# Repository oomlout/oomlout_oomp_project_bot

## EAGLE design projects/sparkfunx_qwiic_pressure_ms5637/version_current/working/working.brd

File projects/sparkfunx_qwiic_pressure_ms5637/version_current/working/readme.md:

# OOMP Project  
## Qwiic_Pressure-MS5637  by sparkfunX  
  
oomp key: oomp_projects_flat_sparkfunx_qwiic_pressure_ms5637  
(snippet of original readme)  
  
SparkFun Qwiic Pressure with MS5637  
========================================  

[*SparkX Pressure Sensor (Qwiic) - MS5637 (SPX-14688)*](https://www.sparkfun.com/products/14688)  
  
MEMs based barometric pressure sensors are quite common these days. The Qwiic Pressure Sensor with the MS5637 shines by being the most sensitive barometric pressure sensor we have come across. It is capable of detecting the difference in 13cm of air! And the MS5637 is low cost and easy to use.  
  
The Qwiic Pressure Sensor for the MS5637 is a very sensitive, fully calibrated, low power, easy to use barometric pressure sensor capable of detecting a change of as little as 13cm of air! The Qwiic Pressure Sensor is perfect for home weather stations, detecting changes in altitude, and pneumatic based switches or actuators.  
  
The original manufacturer TE has written a great Arduino library for the device. We've added a heap of examples and new functions to make the sensor even easier to use. Search the Arduino Library manager for 'SparkFun MS5637' to get the latest library features.  
  
This board is one of our many [Qwiic](https://www.sparkfun.com/qwiic) compatible boards! Simply plug and go. No soldering, no figuring out which is SDA or SCL, and no voltage regulation or translation required!  
  
SparkFun labored with love to create this code. Feel like supporting open source ha  
  full source readme at [readme_src.md](readme_src.md)  
  
source repo at: [https://github.com/sparkfunX/Qwiic_Pressure-MS5637](https://github.com/sparkfunX/Qwiic_Pressure-MS5637)  
## Board  

## Schematic  

[schematic pdf](working_schematic.pdf)  
## Images

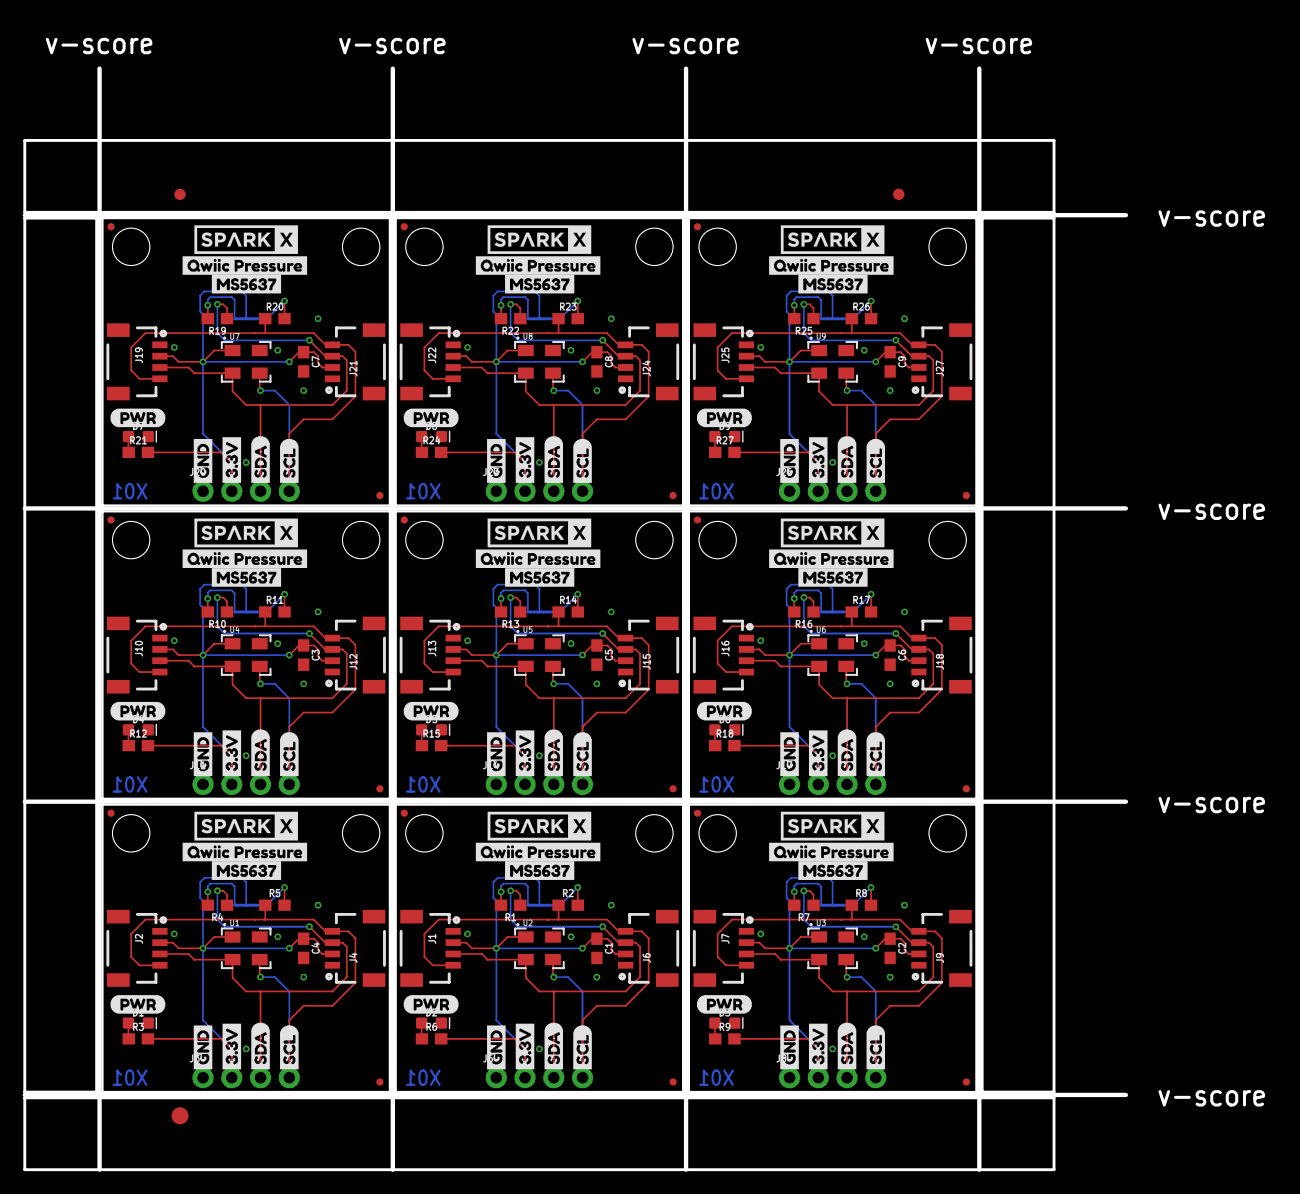
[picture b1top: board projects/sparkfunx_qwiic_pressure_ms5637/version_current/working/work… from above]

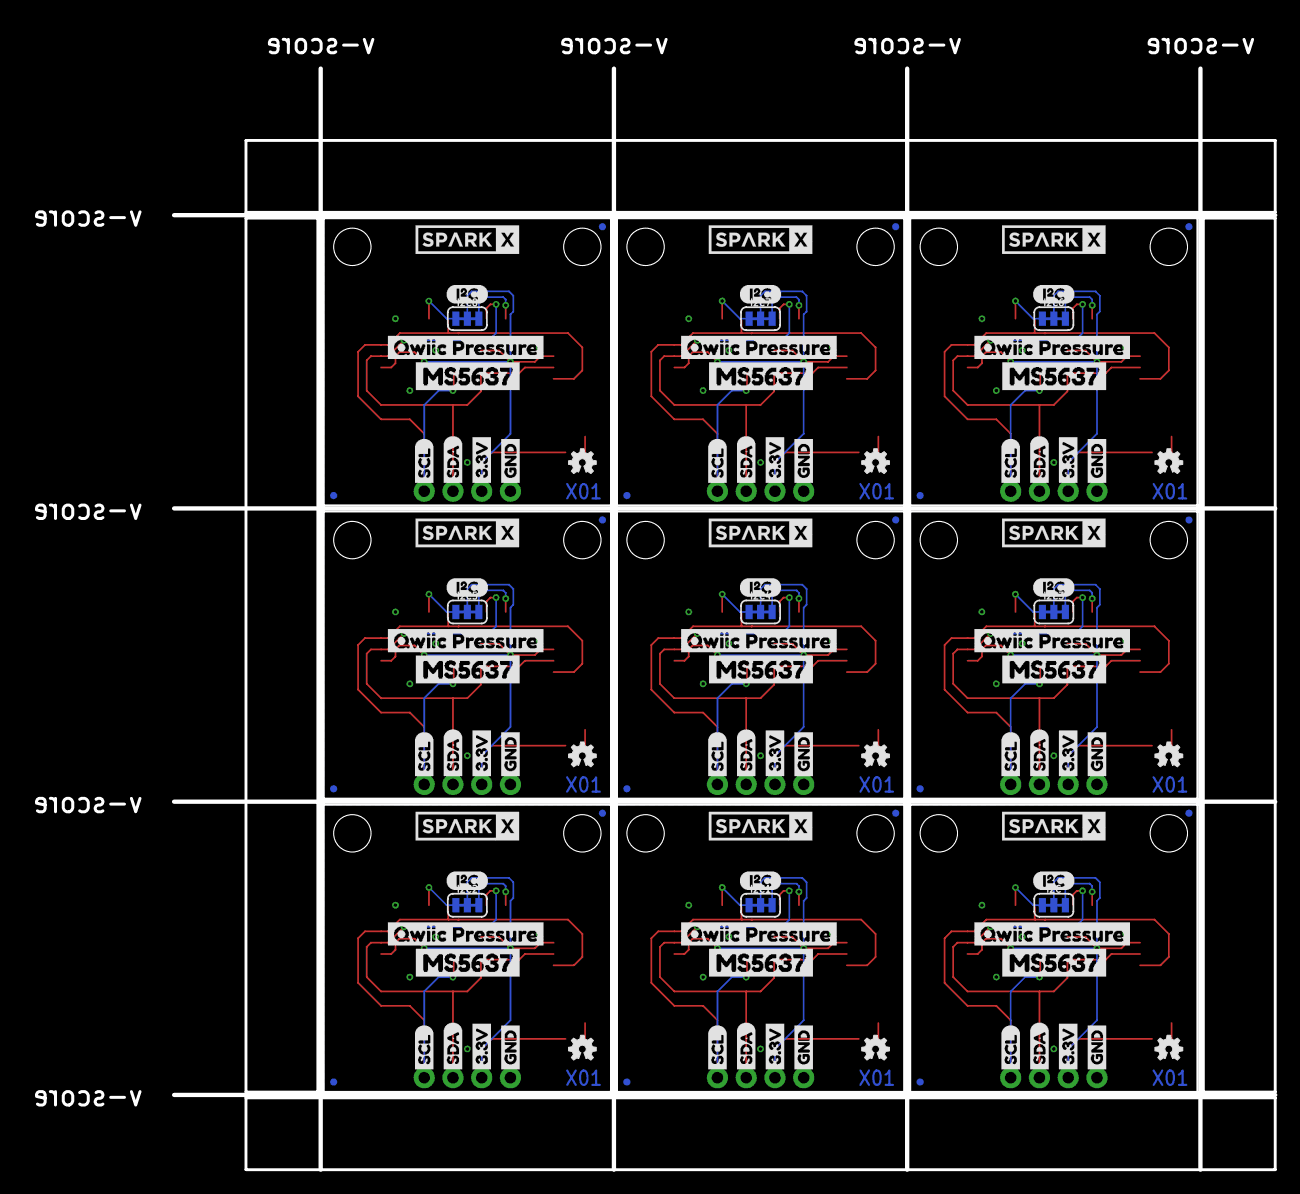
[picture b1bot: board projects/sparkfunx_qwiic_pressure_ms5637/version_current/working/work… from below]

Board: 2 copper layers, 97.3 x 97.3 mm, 300 parts (108 on the bottom side), 63 nets.

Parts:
C1, C2, C3, C4, C5, C6, C7, C8, C9: 0.1uF; 0603
D1, D2, D3, D4, D5, D6, D7, D8, D9: RED; LED-0603
E$1, E$2: FIDUCIAL-1X2
E$3: FIDUCIAL-1.5X3
I2C, I2C1, I2C2, I2C3, I2C4, I2C5, I2C6, I2C7, I2C8: SMT-JUMPER_3_2-NC_TRACE_SILK
J1, J2, J4, J6, J7, J9, J10, J12, J13, J15, J16, J18, J19, J21, J22, J24, J25, J27: 1X04_1MM_RA
J3, J5, J8, J11, J14, J17, J20, J23, J26: PTH; 1X04_NO_SILK
JP1, JP2, JP5, JP6, JP9, JP10, JP11, JP12, JP15, JP16, JP17, JP18, JP21, JP22, JP23, JP24, JP27, JP28, JP29, JP30, JP33, JP34, JP35, JP36, JP39, JP40, JP41, JP42, JP45, JP46, JP47, JP48, JP51, JP52, JP53, JP54: FIDUCIALUFIDUCIAL; MICRO-FIDUCIAL
JP3, JP4, JP7, JP8, JP13, JP14, JP19, JP20, JP25, JP26, JP31, JP32, JP37, JP38, JP43, JP44, JP49, JP50: STAND-OFF
LOGO1, LOGO2, LOGO3, LOGO4, LOGO5, LOGO6, LOGO7, LOGO8, LOGO9: OSHW-LOGOMINI; OSHW-LOGO-MINI
R1, R2, R4, R5, R7, R8, R10, R11, R13, R14, R16, R17, R19, R20, R22, R23, R25, R26: 2.2k; 0603
R3, R6, R9, R12, R15, R18, R21, R24, R27: 1k; 0603
U1, U2, U3, U4, U5, U6, U7, U8, U9: MS5637
U$1, U$2, U$9, U$12, U$33, U$34, U$49, U$50, U$65, U$66, U$81, U$82, U$97, U$98, U$113, U$114, U$129, U$130: SPARKX-LOGO4; SPARKX-MEDIUM
U$3, U$16, U$19, U$22, U$36, U$39, U$52, U$55, U$68, U$71, U$84, U$87, U$100, U$103, U$116, U$119, U$132, U$135: GND1
U$4, U$15, U$20, U$21, U$35, U$40, U$51, U$56, U$67, U$72, U$83, U$88, U$99, U$104, U$115, U$120, U$131, U$136: 3#3V2
U$5, U$18, U$23, U$27, U$38, U$41, U$54, U$57, U$70, U$73, U$86, U$89, U$102, U$105, U$118, U$121, U$134, U$137: SDA8
U$6, U$17, U$24, U$26, U$37, U$42, U$53, U$58, U$69, U$74, U$85, U$90, U$101, U$106, U$117, U$122, U$133, U$138: SCL9
U$7, U$14, U$30, U$31, U$46, U$47, U$62, U$63, U$78, U$79, U$94, U$95, U$110, U$111, U$126, U$127, U$142, U$143: MS56371
U$8, U$13, U$29, U$32, U$45, U$48, U$61, U$64, U$77, U$80, U$93, U$96, U$109, U$112, U$125, U$128, U$141, U$144: QWIIC_PRESSURE0
U$10, U$25, U$43, U$59, U$75, U$91, U$107, U$123, U$139: (PWR)
U$11, U$28, U$44, U$60, U$76, U$92, U$108, U$124, U$140: (I_SUPER2_C)

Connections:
3.3V: C4.1, I2C.2, J2.2, J3.2, J4.2, R3.2, U1.1
3.3V1: C1.1, I2C1.2, J1.2, J5.2, J6.2, R6.2, U2.1
3.3V2: C2.1, I2C2.2, J7.2, J8.2, J9.2, R9.2, U3.1
3.3V3: C3.1, I2C3.2, J10.2, J11.2, J12.2, R12.2, U4.1
3.3V4: C5.1, I2C4.2, J13.2, J14.2, J15.2, R15.2, U5.1
3.3V5: C6.1, I2C5.2, J16.2, J17.2, J18.2, R18.2, U6.1
3.3V6: C7.1, I2C6.2, J19.2, J20.2, J21.2, R21.2, U7.1
3.3V7: C8.1, I2C7.2, J22.2, J23.2, J24.2, R24.2, U8.1
3.3V8: C9.1, I2C8.2, J25.2, J26.2, J27.2, R27.2, U9.1
GND: C4.2, D1.C, J2.1, J3.1, J4.1, U1.4
GND1: C1.2, D2.C, J1.1, J5.1, J6.1, U2.4
GND2: C2.2, D3.C, J7.1, J8.1, J9.1, U3.4
GND3: C3.2, D4.C, J10.1, J11.1, J12.1, U4.4
GND4: C5.2, D5.C, J13.1, J14.1, J15.1, U5.4
GND5: C6.2, D6.C, J16.1, J17.1, J18.1, U6.4
GND6: C7.2, D7.C, J19.1, J20.1, J21.1, U7.4
GND7: C8.2, D8.C, J22.1, J23.1, J24.1, U8.4
GND8: C9.2, D9.C, J25.1, J26.1, J27.1, U9.4
unnamed: I2C.1, R5.2
unnamed: I2C.3, R4.2
unnamed: D1.A, R3.1
unnamed: I2C1.1, R2.2
unnamed: I2C1.3, R1.2
unnamed: D2.A, R6.1
unnamed: I2C2.1, R8.2
unnamed: I2C2.3, R7.2
unnamed: D3.A, R9.1
unnamed: I2C3.1, R11.2
unnamed: I2C3.3, R10.2
unnamed: D4.A, R12.1
unnamed: I2C4.1, R14.2
unnamed: I2C4.3, R13.2
unnamed: D5.A, R15.1
unnamed: I2C5.1, R17.2
unnamed: I2C5.3, R16.2
unnamed: D6.A, R18.1
unnamed: I2C6.1, R20.2
unnamed: I2C6.3, R19.2
unnamed: D7.A, R21.1
unnamed: I2C7.1, R23.2
unnamed: I2C7.3, R22.2
unnamed: D8.A, R24.1
unnamed: I2C8.1, R26.2
unnamed: I2C8.3, R25.2
unnamed: D9.A, R27.1
SCL: J2.4, J3.4, J4.4, R5.1, U1.3
SCL1: J1.4, J5.4, J6.4, R2.1, U2.3
SCL2: J7.4, J8.4, J9.4, R8.1, U3.3
SCL3: J10.4, J11.4, J12.4, R11.1, U4.3
SCL4: J13.4, J14.4, J15.4, R14.1, U5.3
SCL5: J16.4, J17.4, J18.4, R17.1, U6.3
SCL6: J19.4, J20.4, J21.4, R20.1, U7.3
SCL7: J22.4, J23.4, J24.4, R23.1, U8.3
SCL8: J25.4, J26.4, J27.4, R26.1, U9.3
SDA: J2.3, J3.3, J4.3, R4.1, U1.2
SDA1: J1.3, J5.3, J6.3, R1.1, U2.2
SDA2: J7.3, J8.3, J9.3, R7.1, U3.2
SDA3: J10.3, J11.3, J12.3, R10.1, U4.2
SDA4: J13.3, J14.3, J15.3, R13.1, U5.2
SDA5: J16.3, J17.3, J18.3, R16.1, U6.2
SDA6: J19.3, J20.3, J21.3, R19.1, U7.2
SDA7: J22.3, J23.3, J24.3, R22.1, U8.2
SDA8: J25.3, J26.3, J27.3, R25.1, U9.2

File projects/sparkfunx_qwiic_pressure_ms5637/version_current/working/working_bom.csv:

"Id";"Designator";"Footprint";"Quantity";"Designation";"Supplier and ref";
1;"J9,J4,J2,J27,J22,J24,J13,J16,J7,J15,J10,J19,J21,J6,J18,J25,J1,J12";"1X04_1MM_RA";18;"";;;
2;"R18,R9,R21,R15,R12,R24,R3,R27,R6";"0603";9;"1k";;;
3;"U$91,U$123,U$25,U$59,U$75,U$139,U$43,U$10,U$107";"(PWR)";9;"";;;
4;"U$102,U$118,U$70,U$38,U$86,U$134,U$54,U$18,U$27,U$105,U$41,U$23,U$89,U$121,U$57,U$73,U$137,U$5";"SDA8";18;"";;;
5;"J14,J23,J3,J5,J26,J11,J8,J17,J20";"1X04_NO_SILK";9;"PTH";;;
6;"JP44,JP8,JP50,JP37,JP26,JP25,JP49,JP20,JP43,JP32,JP14,JP7,JP13,JP3,JP19,JP31,JP4,JP38";"STAND-OFF";18;"STAND-OFF";;;
7;"U5,U4,U2,U6,U7,U3,U9,U1,U8";"MS5637";9;"MS5637";;;
8;"R11,R26,R14,R17,R19,R23,R22,R2,R4,R5,R16,R8,R20,R25,R7,R10,R1,R13";"0603";18;"2.2k";;;
9;"U$8,U$144,U$64,U$80,U$128,U$32,U$48,U$112,U$96,U$77,U$13,U$109,U$93,U$29,U$125,U$61,U$45,U$141";"QWIIC_PRESSURE0";18;"";;;
10;"JP15,JP10,JP16,JP2,JP9,JP46,JP33,JP6,JP34,JP27,JP45,JP21,JP22,JP28,JP52,JP39,JP51,JP40,JP35,JP17,JP18,JP53,JP48,JP23,JP5,JP1,JP41,JP54,JP29,JP42,JP12,JP47,JP36,JP24,JP30,JP11";"MICRO-FIDUCIAL";36;"FIDUCIALUFIDUCIAL";;;
11;"U$21,U$35,U$99,U$67,U$115,U$15,U$131,U$51,U$83,U$88,U$136,U$56,U$20,U$104,U$72,U$40,U$4,U$120";"3#3V2";18;"";;;
12;"U$116,U$36,U$16,U$68,U$52,U$132,U$22,U$84,U$100,U$103,U$39,U$3,U$55,U$135,U$119,U$71,U$87,U$19";"GND1";18;"";;;
13;"U$95,U$31,U$143,U$7,U$47,U$127,U$63,U$79,U$111,U$126,U$14,U$94,U$30,U$62,U$142,U$46,U$78,U$110";"MS56371";18;"";;;
14;"U$69,U$117,U$101,U$37,U$133,U$26,U$17,U$85,U$53,U$24,U$58,U$90,U$74,U$122,U$106,U$138,U$42,U$6";"SCL9";18;"";;;
15;"C8,C4,C1,C3,C2,C9,C7,C5,C6";"0603";9;"0.1uF";;;
16;"D9,D5,D7,D8,D1,D2,D4,D3,D6";"LED-0603";9;"RED";;;
17;"E$2,E$1";"FIDUCIAL-1X2";2;"";;;
18;"U$50,U$130,U$1,U$34,U$98,U$82,U$114,U$12,U$66,U$2,U$49,U$81,U$9,U$113,U$65,U$33,U$129,U$97";"SPARKX-MEDIUM";18;"SPARKX-LOGO4";;;
19;"E$3";"FIDUCIAL-1.5X3";1;"";;;
20;"I2C1,I2C8,I2C6,I2C5,I2C2,I2C7,I2C0,I2C4,I2C3";"SMT-JUMPER_3_2-NC_TRACE_SILK";9;"";;;
21;"LOGO7,LOGO4,LOGO5,LOGO3,LOGO6,LOGO2,LOGO9,LOGO8,LOGO1";"OSHW-LOGO-MINI";9;"OSHW-LOGOMINI";;;
22;"U$92,U$76,U$60,U$140,U$124,U$28,U$44,U$11,U$108";"(I_SUPER2_C)";9;"";;;

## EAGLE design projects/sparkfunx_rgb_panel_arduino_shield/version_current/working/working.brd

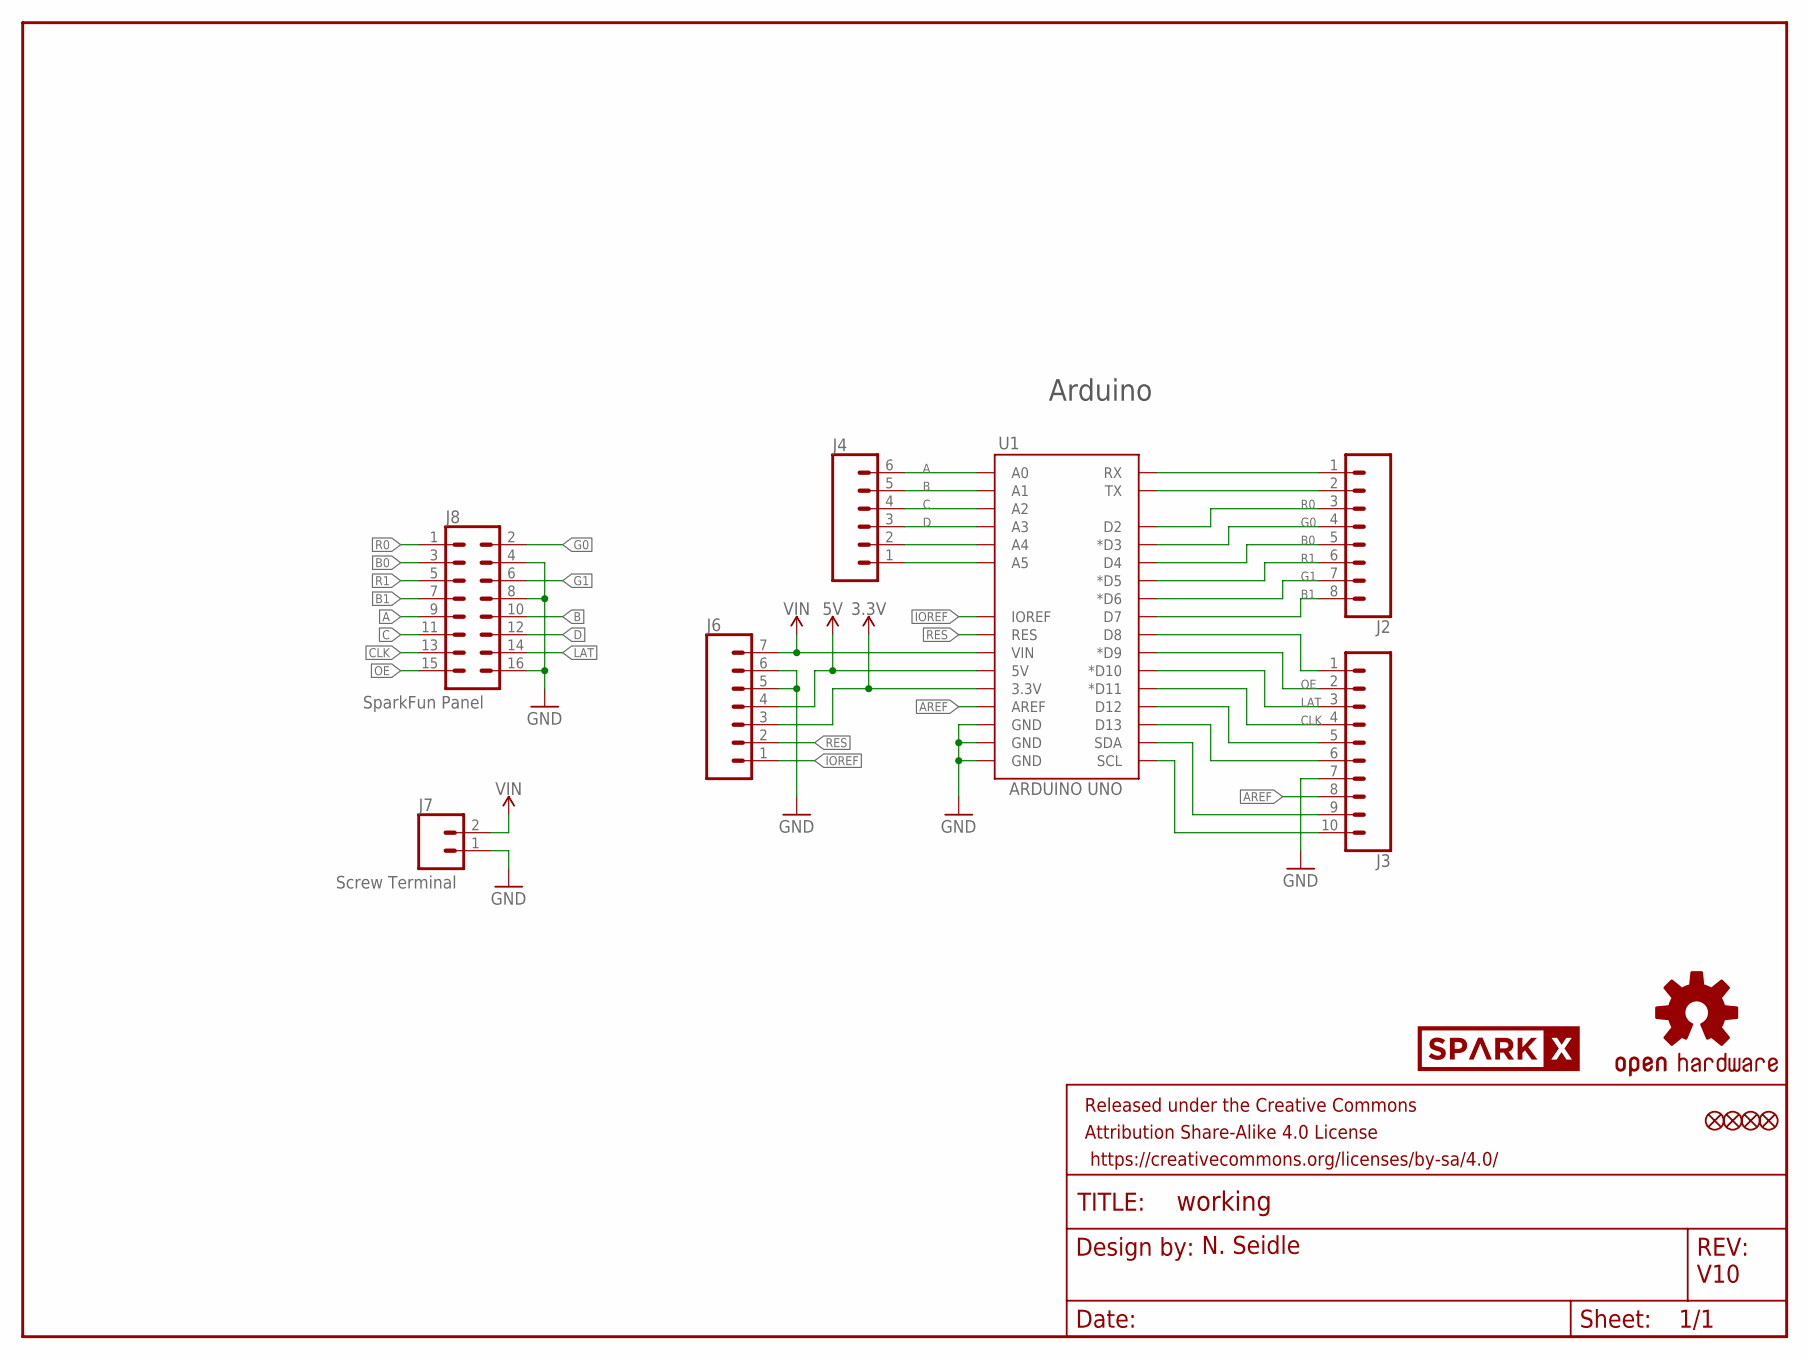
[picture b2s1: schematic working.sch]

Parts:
FD1, FD2, FD3, FD4: FIDUCIAL1X2; FIDUCIAL-1X2
FRAME1: FRAME-LETTER; CREATIVE_COMMONS
J2: CONN_08NO_SILK_FEMALE_PTH; 1X08_NO_SILK
J3: CONN_10NO_SILK_PTH_FEMALE; 1X10_NO_SILK
J4: CONN_06NO_SILK_FEMALE_PTH; 1X06_NO_SILK
J6: CONN_07NO_SILK; 1X07_NO_SILK
J7: Screw Terminal; SCREWTERMINAL-5MM-2
J8: SparkFun Panel; 2X8-SHROUDED_LOCK
LOGO1: OSHW-LOGOMINI; OSHW-LOGO-MINI
U1: ARDUINO UNO; UNO_R3_SHIELD_NOLABELS
U$91: SPARKX-LOGO4; SPARKX-MEDIUM

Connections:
3.3V: J6.3, U1.3.3V
5V: J6.4, U1.5V
A: J4.6, J8.9, U1.A0
A4: J4.2, U1.A4
A5: J4.1, U1.A5
AREF: J3.8, U1.AREF
B: J4.5, J8.10, U1.A1
B0: J2.5, J8.3, U1.D4
B1: J2.8, J8.7, U1.D7
C: J4.4, J8.11, U1.A2
CLK: J3.4, J8.13, U1.D11 (*D11)
D: J4.3, J8.12, U1.A3
D8: J3.1, U1.D8
D12: J3.5, U1.D12
D13: J3.6, U1.D13
G0: J2.4, J8.2, U1.D3 (*D3)
G1: J2.7, J8.6, U1.D6 (*D6)
GND: J3.7, J6.5, J6.6, J7.1, J8.4, J8.8, J8.16, U1.GND@0 (GND), U1.GND@1 (GND), U1.GND@2 (GND)
IOREF: J6.1, U1.IOREF
LAT: J3.3, J8.14, U1.D10 (*D10)
OE: J3.2, J8.15, U1.D9 (*D9)
R0: J2.3, J8.1, U1.D2
R1: J2.6, J8.5, U1.D5 (*D5)
RES: J6.2, U1.RES
RX: J2.1, U1.RX
SCL1: J3.10, U1.SCL
SDA1: J3.9, U1.SDA
TX: J2.2, U1.TX
VIN: J6.7, J7.2, U1.VIN

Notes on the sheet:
N. Seidle
Arduino
V10

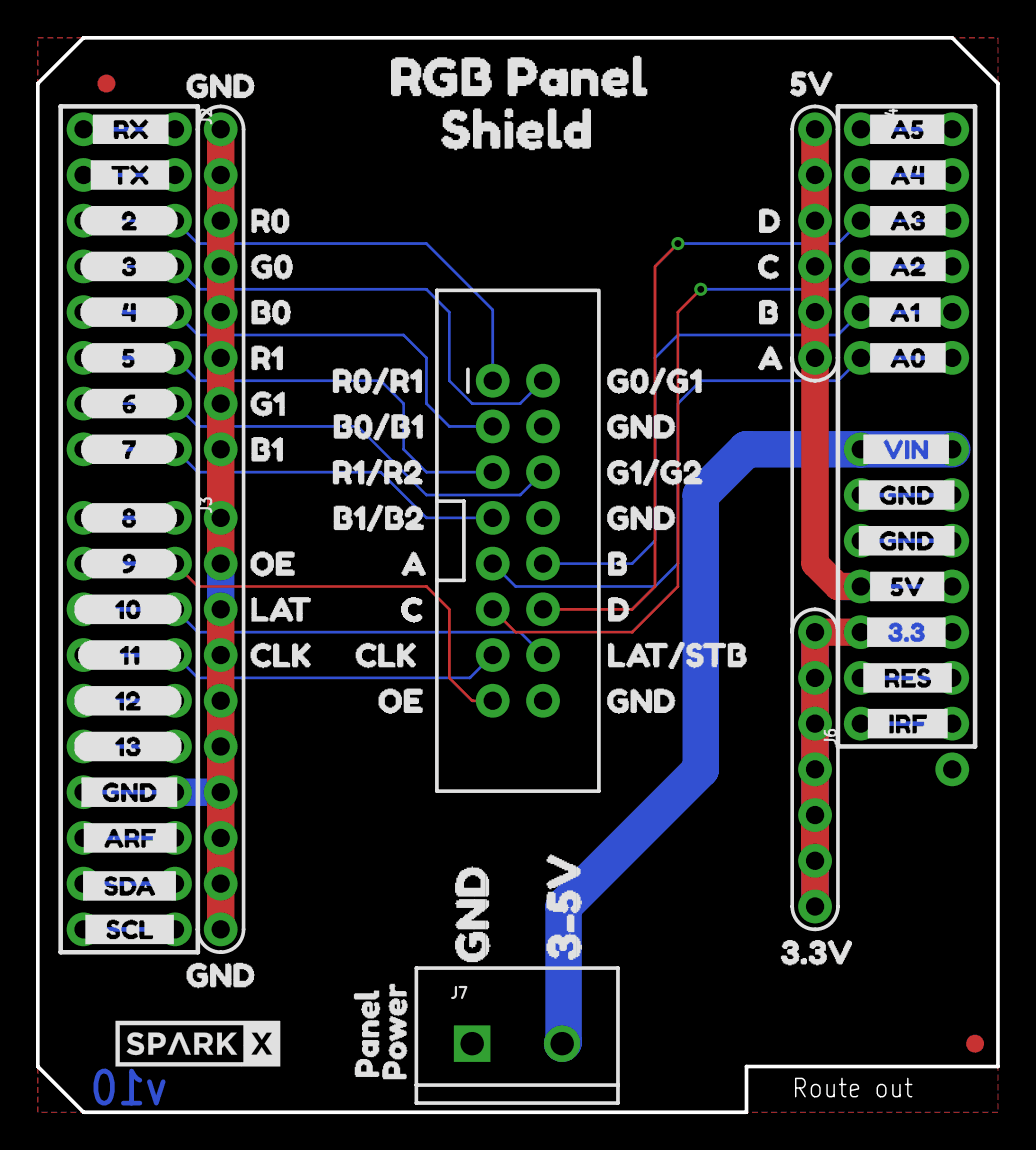
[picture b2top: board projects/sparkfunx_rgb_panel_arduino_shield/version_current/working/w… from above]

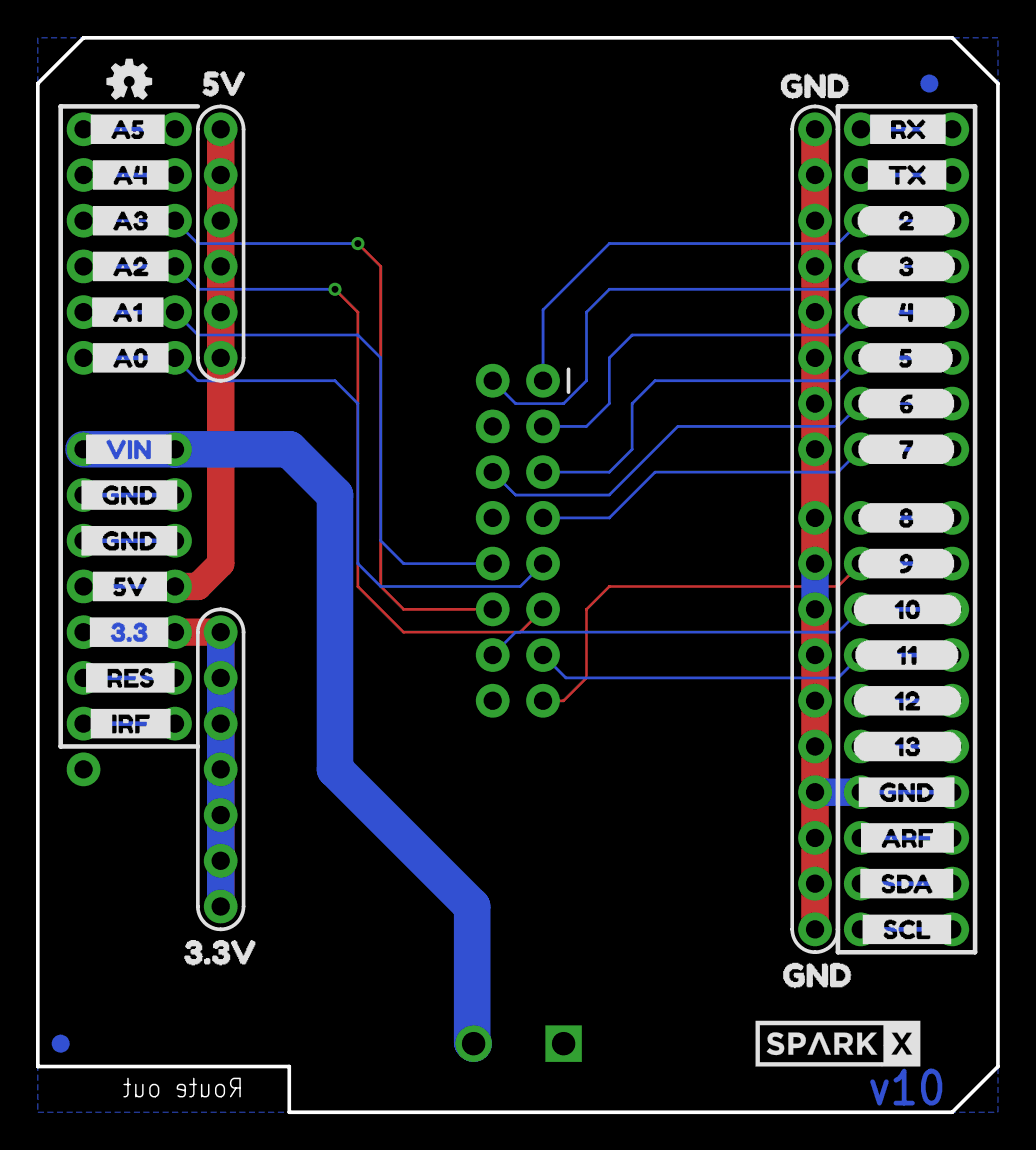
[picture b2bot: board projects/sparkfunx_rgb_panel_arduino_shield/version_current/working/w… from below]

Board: 2 copper layers, 53.3 x 59.7 mm, 122 parts (39 on the bottom side), 29 nets.

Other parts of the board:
U$1, U$34: D42
U$2, U$128: SPARKX-MEDIUM
U$3, U$32, U$113: C37
U$4, U$38: GND48
U$5: 3#5V3
U$6, U$79: ____2____1
U$7, U$80: ____3____3
U$8, U$81: ____4____4
U$9, U$82: ____5____5
U$10, U$83: ____6____6
U$11: GND2
U$12, U$84: ____7____7
U$13, U$85: ____8____8
U$14, U$86: ____9____9
U$15, U$87: ____10____10
U$16: PANEL0
U$17, U$88: ____11____11
U$18, U$89: ____12____12
U$19: POWER1
U$20, U$90: ____13____13
U$21, U$22, U$37, U$108, U$109: GND40
U$23: RGB_PANEL2
U$24, U$73: __RX__0
U$25, U$110: 3#3V46
U$26, U$107: 5V47
U$27, U$45: __3#3__27
U$28, U$115: A36
U$29: B0#B132
U$30: B1#B235
U$31, U$114: B43
U$33, U$121: CLK38
U$35: G0#G145
U$36: G1#G244
U$39: LAT#STB41
U$40, U$122: OE39
U$41: R0#R131
U$42: R1#R234
U$43, U$48: __5V__26
U$44, U$62: __A0__23
U$46, U$63: __A1__22
U$47, U$64: __A2__21
U$49, U$65: __A3__20
U$50, U$66: __A4__19
U$51, U$72: __A5__18
U$52, U$74: __ARF__15
U$53, U$75: __GND__14
U$54, U$55, U$67, U$68: __GND__25
U$56, U$71: __IRF__29
U$57, U$69: __RES__28
U$58, U$76: __SCL__17
U$59, U$77: __SDA__16
U$60, U$78: __TX__0
U$61, U$70: __VIN__24
U$112: B15
U$116: B03
U$117: G01
U$118: G14
U$119: R00
U$120: R12
U$123: LAT0
U$124: SHIELD0

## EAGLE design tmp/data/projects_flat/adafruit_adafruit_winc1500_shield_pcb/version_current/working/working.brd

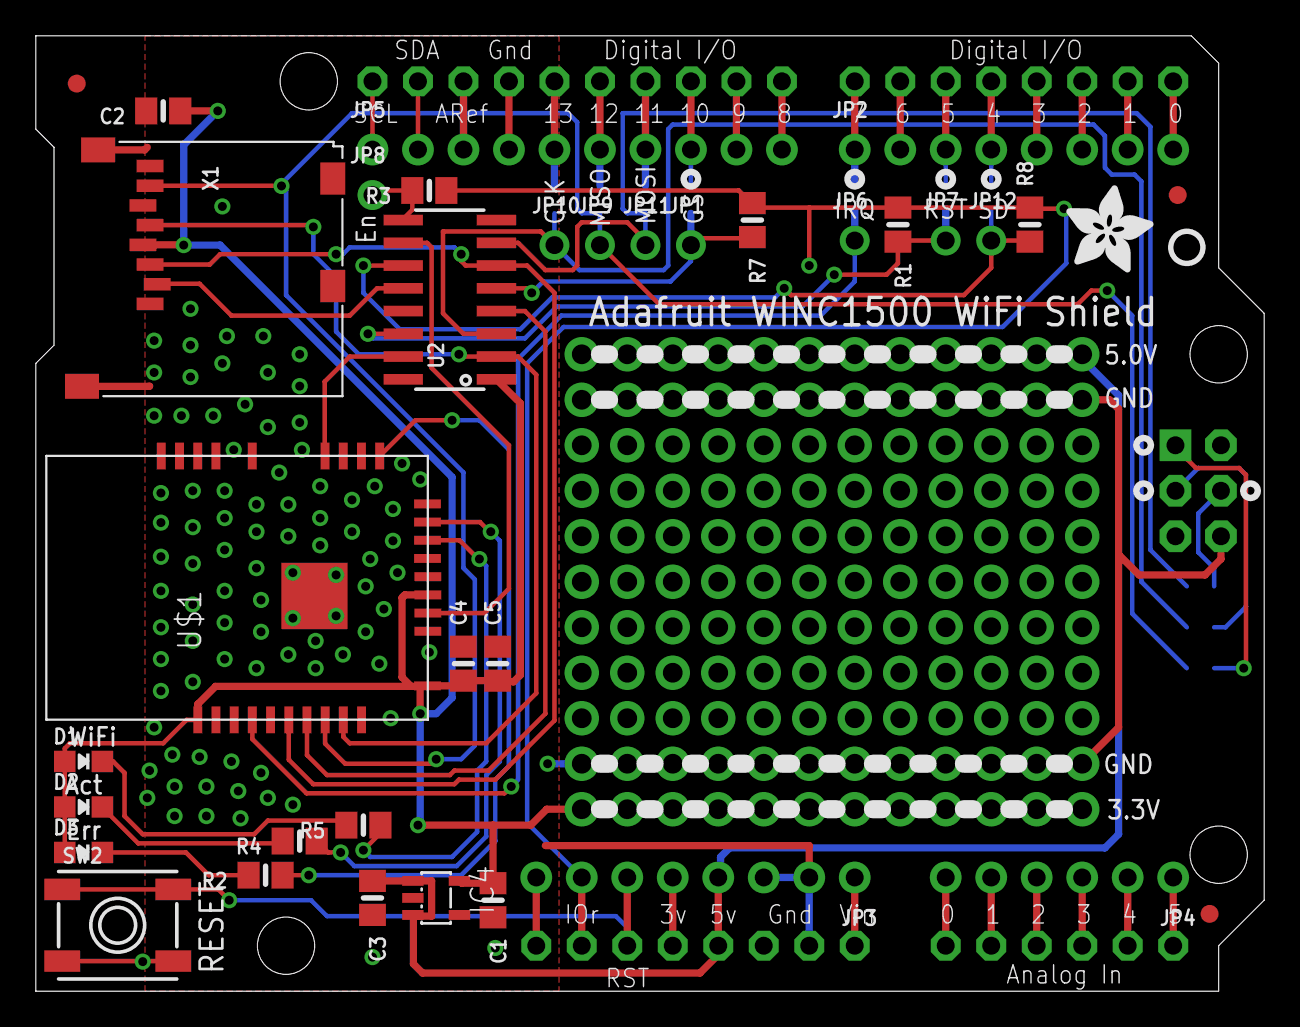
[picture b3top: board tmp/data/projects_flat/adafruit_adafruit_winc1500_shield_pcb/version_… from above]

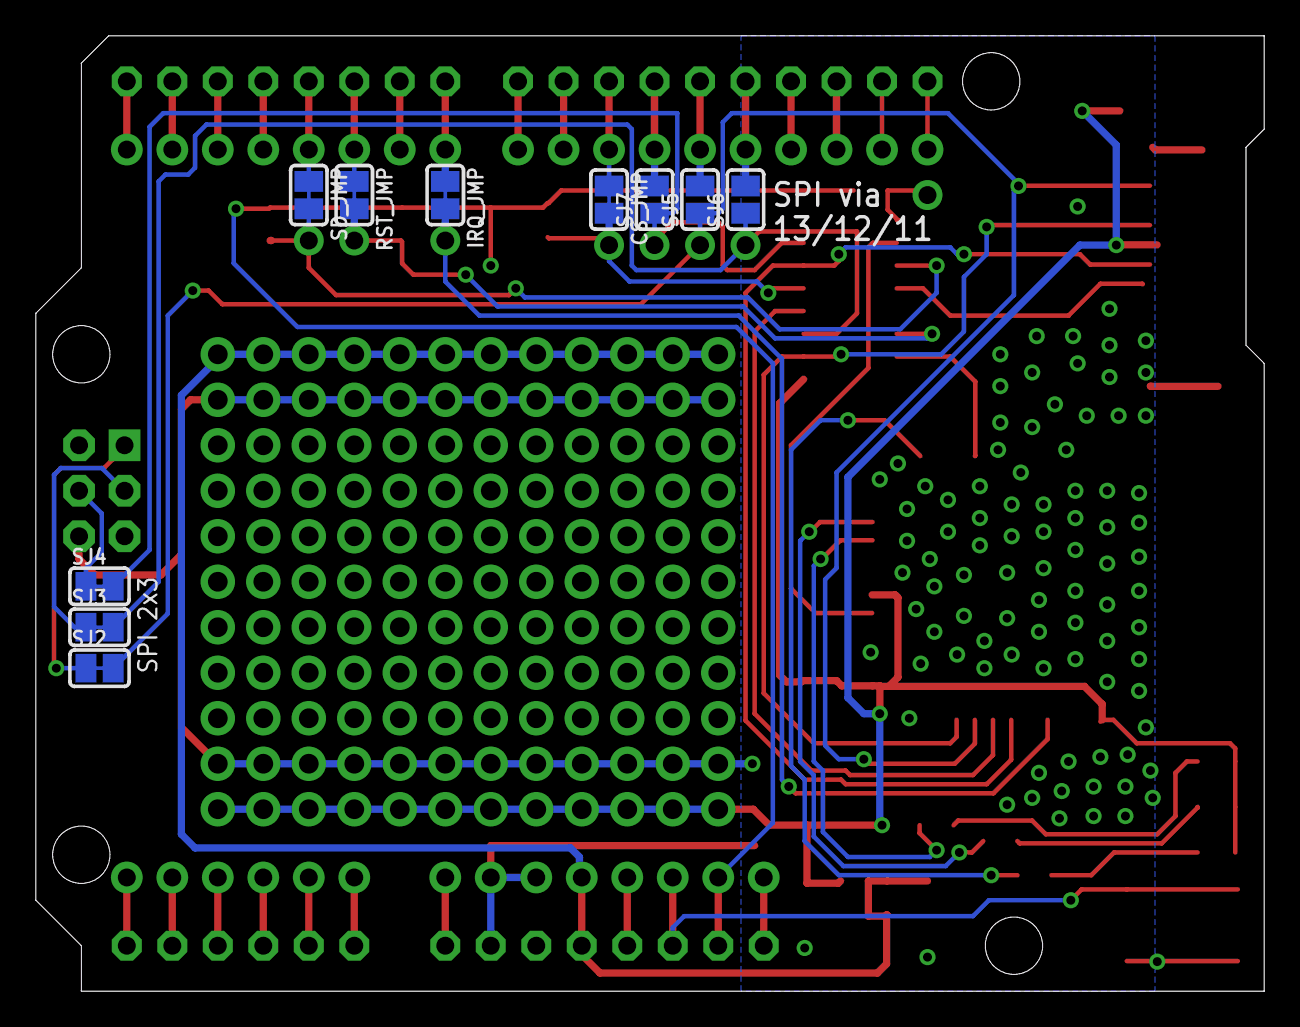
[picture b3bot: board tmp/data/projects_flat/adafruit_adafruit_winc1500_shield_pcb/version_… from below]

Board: 2 copper layers, 68.6 x 53.3 mm, 48 parts (10 on the bottom side), 54 nets.

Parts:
C1, C2, C3, C4: 10uF; 0805-NO
C5: 1uF; 0805-NO
CS_JMP: SOLDERJUMPER_CLOSEDWIRE
D1: green; CHIPLED_0805_NOOUTLINE
D2: Yellow; CHIPLED_0805_NOOUTLINE
D3: Red; CHIPLED_0805_NOOUTLINE
FID1, FID2, FID3: FIDUCIAL_1MM
IC4: AP2112-3.3; SOT23-5L
IRQ_JMP: SOLDERJUMPER_CLOSEDWIRE
JP1, JP6, JP7, JP8, JP9, JP10, JP11, JP12: 1X01_ROUND
JP2, JP3: 1X08_ROUND_70
JP4: 1X06_ROUND_70
JP5: 1X10_ROUND70
M1: ARDUINO_R3_ICSP_NODIM; ARDUINOR3_ICSP_NODIM
R1, R3, R7, R8: 100K; 0805-NO
R2, R4, R5: 1K; 0805-NO
RST_JMP: SOLDERJUMPER_CLOSEDWIRE
SD_JMP: SOLDERJUMPER_CLOSEDWIRE
SJ2: ICSP_MISO; SOLDERJUMPER_CLOSEDWIRE
SJ3: ISCP_SCLK; SOLDERJUMPER_CLOSEDWIRE
SJ4: ICSP_MOSI; SOLDERJUMPER_CLOSEDWIRE
SJ5: D12_MISO; SOLDERJUMPER_REFLOW_NOPASTE
SJ6: D13_SCLK; SOLDERJUMPER_REFLOW_NOPASTE
SJ7: D11_MOSI; SOLDERJUMPER_REFLOW_NOPASTE
SW2: Tactile; EVQ-Q2_SMALLER
U2: 74HC4050; SOIC16
U$1: ATWINC1500_MR210PB; ATWINC1500_MR210PA
U$9: ADAFRUIT_5MM
U$21: PCBFEAT-REV-040
X1: microSd; MICROSD

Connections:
3.3V: C1.1, C2.1, C4.1, C5.1, D1.A, D2.A, D3.A, IC4.5, U2.1, U$1.J10, U$1.J20, U$1.J23, X1.4
+3V: JP3.5, M1.3V
+5V: C3.1, IC4.1, IC4.3, JP3.4, M1.5V
A0: JP4.6, M1.A0
A1: JP4.5, M1.A1
A2: JP4.4, M1.A2
A3: JP4.3, M1.A3
A4: JP4.2, M1.A4
A5: JP4.1, M1.A5
AREF: JP5.3, M1.AREF
CS_3V: U2.4, U$1.J16
D0: JP2.8, M1.D0
D1: JP2.7, M1.D1
D2: JP2.6, M1.D2
D3: JP2.5, M1.D3
D4: JP2.4, M1.D4, SD_JMP.1
D5: JP2.3, M1.D5, RST_JMP.1
D6: JP2.2, M1.D6
D7: IRQ_JMP.1, JP2.1, M1.D7
D8: JP5.10, M1.D8
D9: JP5.9, M1.D9
D10: CS_JMP.1, JP5.8, M1.D10
D11: JP5.7, M1.D11, SJ7.2
D12: JP5.6, M1.D12, SJ5.2
D13: JP5.5, M1.D13, SJ6.2
EN_3V: U2.10, U$1.J22
GND: C1.2, C2.2, C3.2, C4.2, C5.2, IC4.2, JP3.2, JP3.3, JP5.4, M1.GND, M1.GND@1, M1.GND@3, SW2.A, SW2.A', U2.8, U$1.J9, U$1.J12, U$1.J28, U$1.MTGND, X1.6, X1.MT1, X1.MT2
GPIO15: R5.1, U$1.J26
GPIO16: R4.1, U$1.J27
MISO: JP9.1, SJ2.2, SJ5.1, U$1.J17, X1.7
MISO_ICSP: M1.MISO, SJ2.1
MOSI: JP11.1, SJ4.2, SJ7.1, U2.7
MOSI_3V: U2.6, U$1.J15, X1.3
MOSI_ICSP: M1.MOSI, SJ4.1
unnamed: D3.C, R2.2
unnamed: D2.C, R4.2
unnamed: D1.C, R5.2
unnamed: R2.1, U$1.J1
NC: JP3.8, M1.RESERVED
RESET: JP3.6, M1.RESET, SW2.B, SW2.B'
RST_3V: U2.15, U$1.J4
SCK: JP10.1, SJ3.2, SJ6.1, U2.3
SCK_3V: U2.2, U$1.J18, X1.5
SCK_ICSP: M1.SCK, SJ3.1
SCL: JP5.1, M1.SCL
SDA: JP5.2, M1.SDA
SDCS: JP12.1, R8.1, SD_JMP.2, U2.11
SDCS_3V: U2.12, X1.2
VIN: JP3.1, M1.VIN
VIOREF: JP3.7, M1.IOREF, R1.1, R3.1, R7.1, R8.2
WINC_CS: CS_JMP.2, JP1.1, R7.2, U2.5
WINC_EN: JP8.1, R3.2, U2.9
WINC_IRQ: IRQ_JMP.2, JP6.1, U$1.J13
WINC_RST: JP7.1, R1.2, RST_JMP.2, U2.14

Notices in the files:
projects/tinkerforge_breakout_bricklet/version_current/working/working.sch:
Licensed under CERN OHL v.1.1
Copyright (©) 2011, B.Nordmeyer
Copyright Tinkerforge GmbH 2011.
This documentation describes Open Hardware and is licensed under the
CERN OHL v. 1.1.
parts and their libraries:
SparkFun-Resistors: Licensing: Creative Commons ShareAlike 4.0 International - https://creativecommons.org/licenses/by-sa/4.0
SparkFun-Boards: Licensing: CC v3.0 Share-Alike You are welcome to use this library for commercial purposes.
SparkFun-Aesthetics: Released under the Creative Commons
